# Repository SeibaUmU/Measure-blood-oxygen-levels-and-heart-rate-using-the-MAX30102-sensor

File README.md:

# Measure-blood-oxygen-levels-and-heart-rate-using-the-MAX30102-sensor.
This's just a school subject's project.
## Project Overview

This project is a real-time health monitoring system designed to measure **heart rate (BPM)** and **blood oxygen saturation (SpO₂)** using the **MAX30102 sensor**.

The MAX30102 collects the raw physiological data and transmits it to an **ESP32**, where the measurements are processed and converted into meaningful heart rate and SpO₂ values. The ESP32 then sends the processed data to an **Altera DE2 FPGA development board** using a predefined data frame protocol.

The DE2 receives and processes the data before transmitting it to a **C# GUI application** running on a laptop through a **COM (serial) connection**. The GUI displays the real-time measurements and provides live-time charts for both heart rate and blood oxygen saturation.

The GUI also supports sending control commands to the DE2, such as stopping the measurement process. In addition, measured data can be exported and stored as a **CSV file** for further analysis and record keeping.

### System Architecture

**MAX30102 → ESP32 → Altera DE2 → C# GUI → CSV**

### Main Features

* Real-time heart rate (BPM) measurement
* Real-time blood oxygen saturation (SpO₂) measurement
* MAX30102 sensor data acquisition
* Data processing on ESP32
* Communication between ESP32 and Altera DE2
* Predefined data frame protocol
* Serial communication between DE2 and PC via COM port
* Real-time data visualization using C# GUI
* Live heart rate and SpO₂ charts
* Control commands from GUI to DE2
* Measurement data export to CSV
---

## User Guide

### 1. Installation

1. Run `MAX30102_Setup.exe`.
2. Follow the installation wizard and grant Administrator permission if requested by Windows.
3. After installation, launch **MAX30102 WPF** from the Start Menu or the Desktop shortcut (if created during installation).

### 2. Connecting to the Device

1. Connect the microcontroller board to the computer via USB-UART.
2. Open the application and select the correct COM port corresponding to the device.
3. Set the Baud Rate to `9600`.
4. Click **Connect**. Once the connection is successful, the status will change to Connected.

**If the connection fails:** Check the USB cable, USB-UART driver, selected COM port, and make sure the port is not being used by another application.

### 3. Measuring and Monitoring Data

- **Start:** Sends the measurement start command. The application updates BPM, SpO₂, and the PPG waveform when data is received from the device.
- **Stop:** Stops the measurement process.
- **Reset:** Sends the reset command and clears the displayed statistics and graph data.
- **BPM and SpO₂:** Display the current measurement values. Avg, Min, and Max show the statistics collected during the measurement session.
- **PPG Waveform:** Displays the PPG signal. Move the mouse over the graph to inspect values. Click to pin a marker for comparison.
- **Freeze:** Temporarily pauses graph updates.
- **Clear Pins:** Removes all pinned markers from the graph.

### 4. Communication Test

1. Connect the device and make sure the firmware supports TEST packet loopback.
2. Click **Run Test** to start the test.
3. The application sends 1000 numbered TEST packets sequentially and waits for the firmware to return them.
4. Monitor the progress bar and test results. Packets that are not received back are counted as lost packets.

**Note:** The test requires firmware support for returning TEST packets according to the predefined protocol.

### 5. Data Transmission and Logging

- Open the **Send and Receive** section, enter the message in ASCII text format, and click **Send**.
- **Last Frame Received** displays the most recently received data frame.
- Open the **Log** section to view transmitted and received frames. Click **Clear** to clear the displayed log.

### 6. Data Export

1. After PPG data has been collected, click **Export**.
2. Select the destination folder and choose CSV or TXT format in the save dialog.
3. Check the exported file at the selected location.

### 7. Disconnecting and Additional Notes

- Click **Disconnect** before unplugging the device or closing the application.
- If the USB cable is accidentally disconnected or a connection error occurs, reconnect the device and select the correct COM port again.
- This software is intended for educational, experimental, and signal-monitoring purposes. It is not a substitute for medical devices or professional medical diagnosis.

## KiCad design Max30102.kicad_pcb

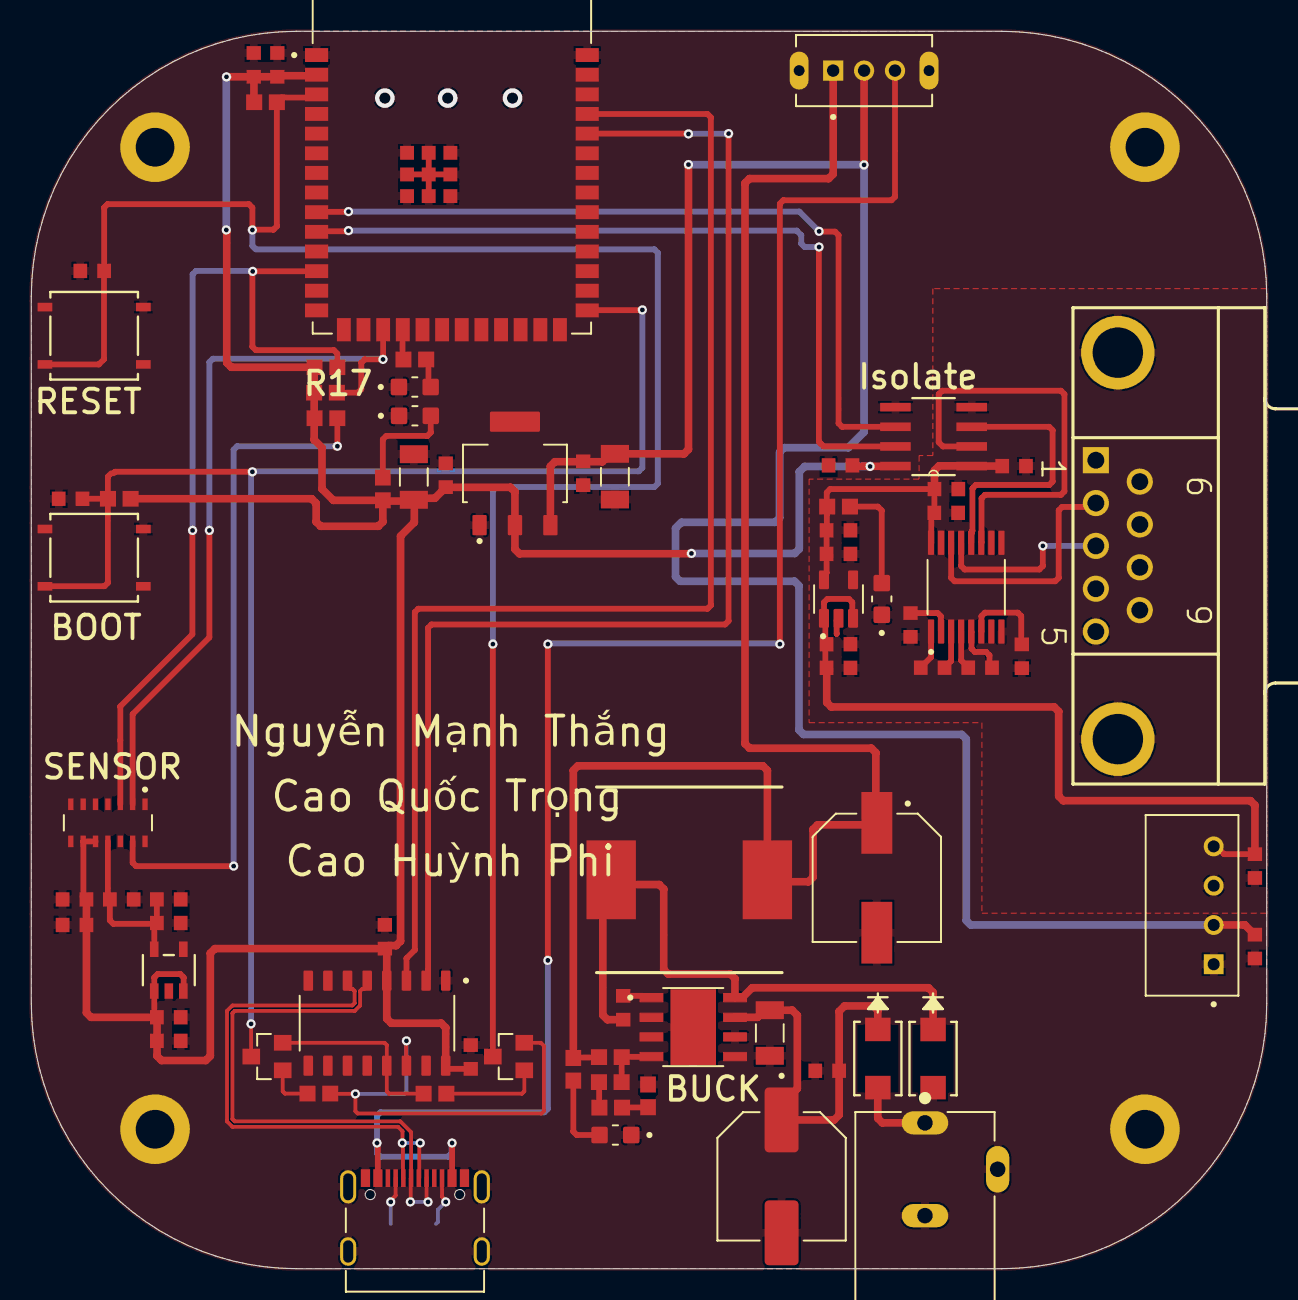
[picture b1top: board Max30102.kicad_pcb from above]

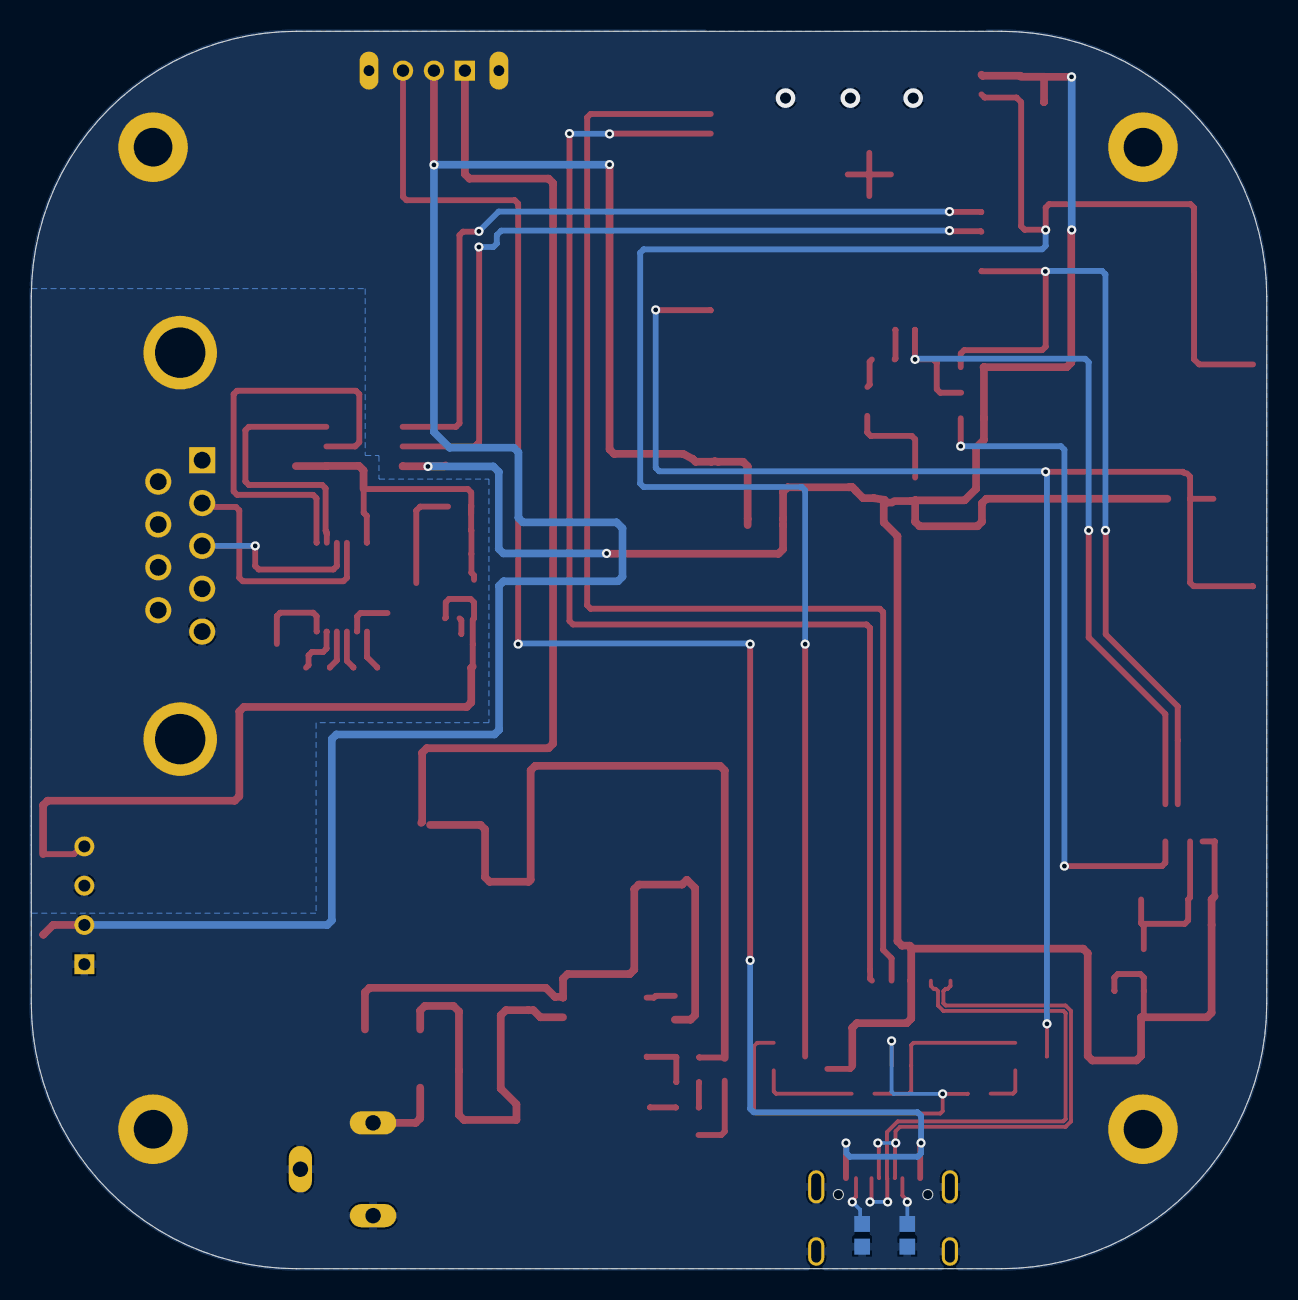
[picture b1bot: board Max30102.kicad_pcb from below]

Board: 2 copper layers, 79.9 x 80.0 mm, 78 parts (2 on the bottom side), 48 nets.

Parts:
BOOT: BOOT; SMT_FS
BUCK: TPS5430; CONV_TPS5430DDAR
C1, C3, C4, C5, C8, C9, C11, C12, C14, C17, C18, C20, C23, C25, C27, C28, C29, C30, C31, C32, C34, C35: 100nF; CAPC1608X90N
C2, C6, C15, C16, C19, C21, C26: 10uF; CAPC1608X90N
C7: 100uF; CAPAE830X1000N
C10, C13: 10uF; CAPC3216X110N
C22: 22uF 25V; CAPC3216X229N
C24: 330uF; CAP_EEEFP1V101AP
C33, C36: 1uF; CAPC1608X90N
CR1, CR2: SSA34; CR_A34-E35AT_VIS
D1, D2, D5: MCU LED; LEDSC125X200X90-2N
D3: BUCK LED; LEDSC125X200X90-2N
Isolate: ADUM1201ARZ; SOIC127P600X175-8N
J1: USB Type-C; AMPHENOL_10155435-00011LF
J2: PJ-102AH; CUI_PJ-102AH
J3: D Connector 9; DSUB1.385-2H9
L1: 22uH; INDPM120120X800N
PS1: 1S4E_0505S1U; CONV_1S4E_0505S1U
Q1, Q2: S8050; SOT-23
R1, R3: 5K1; RESC1607X60N
R2, R4, R6, R7, R11: 10K; RESC1607X60N
R5, R10, R14, R15: 220; RESC1607X60N
R8, R9: 4K7; RESC1607X60N
R12, R13, R16, R17: 1K5; RESC1607X60N
RESET: RESET; SMT_FS
S3: SS12D07VG4; SW_SS12D07VG4
SENSOR: MAX30102EFD+T; XDCR_MAX30101EFD+
U1: ESP32-S3-WROOM-1-N8R8; XCVR_ESP32S3WROOM1N8R8
U2: CH340C; SOIC127P600X180-16N
U4: AMS1117-3.3; SOT229P700X180-4N
U5: AP2127K-1.8TRG1; SOT-23-5_AP2127K_DIO
U8: MAX3232CPW; SOP65P640X120-16N
U9: RT9013-33GB; SOT94P279X129-5N

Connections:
+1.8: C15.2, C18.2, C19.2, SENSOR.11, U5.5
+3.3_ISO: C9.2, C25.2, C26.2, C35.2, C36.2, Isolate.1, R15.2, U8.16, U9.5
+3.3_MCU: C1.2, C2.2, C5.2, C6.2, C12.2, C13.1, C14.2, C16.2, C17.2, C20.2, C21.2, Isolate.8, R2.1, R4.1, R8.1, R9.1, R10.1, R17.1, SENSOR.9, SENSOR.10, U1.2, U2.4, U2.16, U4.2, U5.1, U5.3
+5: C24.1, L1.2, R11.1, R13.1, S3.1
+5_ISO: C32.2, C33.2, C34.2, PS1.4, U9.1, U9.3
+12: BUCK.7, C7.1, C8.2, C22.2, CR1.1
DTR: Q1.2, R7.1, U2.13
EN: C3.2, Q2.3, R2.2, RESET.3, U1.3
ESP_RX: U1.36, U2.2
ESP_TX: U1.37, U2.3
GND: BOOT.2, BUCK.6, BUCK.9, C1.1, C2.1, C3.1, C4.1, C5.1, C6.1, C7.2, C8.1, C10.2, C11.1, C12.1, C13.2, C14.1, C15.1, C16.1, C17.1, C18.1, C19.1, C20.1, C21.1, C22.1, C24.2, C31.1, CR2.2, D1.C, D2.C, D3.C, Isolate.5, J1.A1_B12, J1.B1_A12, J1.SH1, J1.SH2, J1.SH3, J1.SH4, J2.2, J2.3, PS1.1, R1.1, R3.2, R14.2, RESET.2, SENSOR.4, SENSOR.12, U1.1, U1.40, U1.41_1, U1.41_2, U1.41_3, U1.41_4, U1.41_5, U1.41_6, U1.41_7, U1.41_8, U1.41_9, U2.1, U4.1, U5.2
GND1: C9.1, C25.1, C26.1, C27.1, C30.1, C32.1, C33.1, C34.1, C35.1, C36.1, D5.C, Isolate.4, J3.5, J3.10, J3.11, PS1.3, U8.8, U8.10, U8.15, U9.2
INT: R17.2, SENSOR.13
IO0: BOOT.3, C4.2, Q1.3, R4.2, U1.27
NetC23_1: BUCK.8, C23.1, CR2.1, L1.1
NetC23_2: BUCK.1, C23.2
NetC27_2: C27.2, U8.2
NetC28_1: C28.1, U8.3
NetC28_2: C28.2, U8.1
NetC29_1: C29.1, U8.5
NetC29_2: C29.2, U8.4
NetC30_2: C30.2, U8.6
NetCR1_2: CR1.2, J2.1
NetD1_A: D1.A, R5.2
NetD2_A: D2.A, R10.2
NetD3_A: D3.A, R13.2
NetD5_A: D5.A, R15.1
NetJ1_A5: J1.A5, R1.2
NetJ1_B5: J1.B5, R3.1
NetQ1_1: Q1.1, R6.2
NetQ2_1: Q2.1, R7.2
NetR11_2: BUCK.4, R11.2, R12.1
NetR12_2: R12.2, R16.2
NetR14_1: R14.1, R16.1
POWER: C10.1, C11.2, C31.2, PS1.2, S3.2, U4.3
RTS: Q2.2, R6.1, U2.14
RX_DB9: J3.3, U8.13
SCL: R8.2, SENSOR.2, U1.17
SDA: R9.2, SENSOR.3, U1.12
STATUS: R5.1, U1.18
TX_DB9: J3.2, U8.14
UART1_RX: Isolate.6, U1.9
UART1_TX: Isolate.7, U1.10
UART_ISO_RX: Isolate.3, U8.12
UART_ISO_TX: Isolate.2, U8.11
USB+: J1.A4_B9, J1.B4_A9, S3.3
USB_N: J1.A7, J1.B7, U2.6
USB_P: J1.A6, J1.B6, U2.5
